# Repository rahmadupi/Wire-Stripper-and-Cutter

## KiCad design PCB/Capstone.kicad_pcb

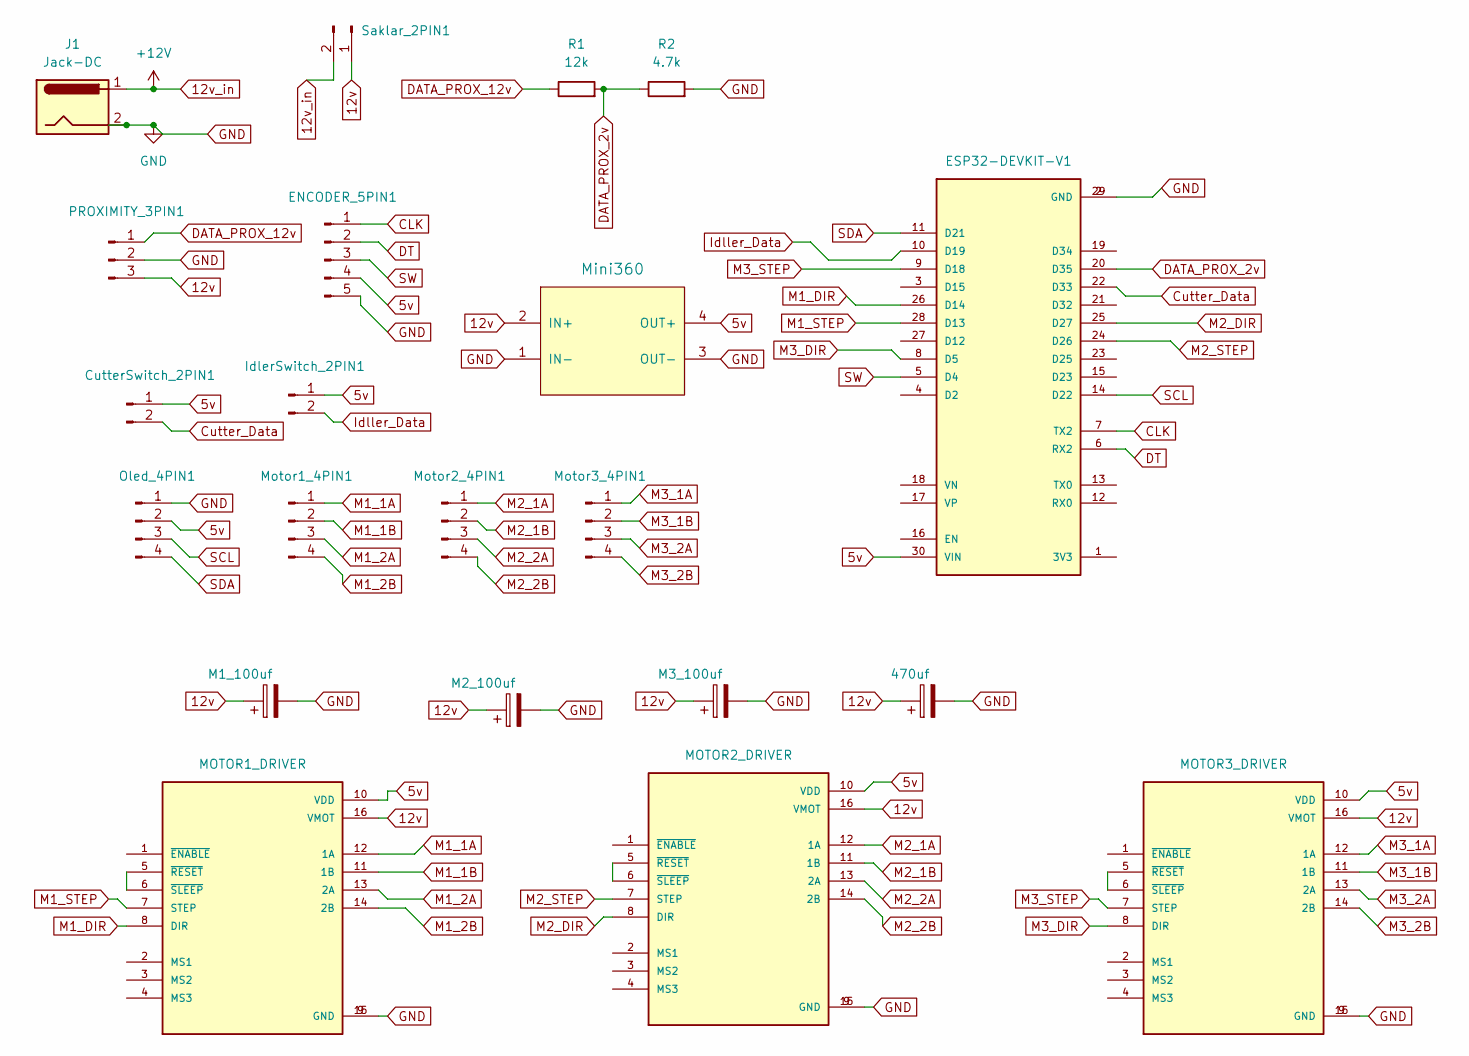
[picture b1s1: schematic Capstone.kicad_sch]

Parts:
C1: M1_100uf; CP_Radial_D4.0mm_P1.50mm
C2: M2_100uf; CP_Radial_D4.0mm_P1.50mm
C3: M3_100uf; CP_Radial_D4.0mm_P1.50mm
C4: 470uf; CP_Radial_D4.0mm_P1.50mm
CutterSwitch_2PIN1: Conn_01x02_Pin; JST_EH_B2B-EH-A_1x02_P2.50mm_Vertical
ENCODER_5PIN1: Conn_01x05_Pin; JST_EH_B5B-EH-A_1x05_P2.50mm_Vertical
IdlerSwitch_2PIN1: Conn_01x02_Pin; JST_EH_B2B-EH-A_1x02_P2.50mm_Vertical
J1: Jack-DC; BarrelJack_Horizontal
Motor1_4PIN1, Motor2_4PIN1, Motor3_4PIN1: Conn_01x04_Pin; JST_EH_B4B-EH-A_1x04_P2.50mm_Vertical
Oled_4PIN1: Conn_01x04_Pin; JST_EH_B4B-EH-A_1x04_P2.50mm_Vertical
PROXIMITY_3PIN1: Conn_01x03_Pin; JST_EH_B3B-EH-A_1x03_P2.50mm_Vertical
R1: 12k; R_Axial_DIN0204_L3.6mm_D1.6mm_P7.62mm_Horizontal
R2: 4.7k; R_Axial_DIN0204_L3.6mm_D1.6mm_P7.62mm_Horizontal
Saklar_2PIN1: Conn_01x02_Pin; JST_EH_B2B-EH-A_1x02_P2.50mm_Vertical
U1: ESP32-DEVKIT-V1; MODULE_ESP32_DEVKIT_V1; PARTREV N/A
U2: Mini360; Mini360_Module
U3: MOTOR1_DRIVER; MODULE_A4988_STEPPER_MOTOR_DRIVER_CARRIER_BLACK
U4: MOTOR2_DRIVER; MODULE_A4988_STEPPER_MOTOR_DRIVER_CARRIER_BLACK
U5: MOTOR3_DRIVER; MODULE_A4988_STEPPER_MOTOR_DRIVER_CARRIER_BLACK

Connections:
5v: CutterSwitch_2PIN1.1, ENCODER_5PIN1.4, IdlerSwitch_2PIN1.1, Oled_4PIN1.2, U1.30 (VIN), U2.4 (OUT+), U3.10 (VDD), U4.10 (VDD), U5.10 (VDD)
12v: C1.1, C2.1, C3.1, C4.1, PROXIMITY_3PIN1.3, Saklar_2PIN1.1, U2.2 (IN+), U3.16 (VMOT), U4.16 (VMOT), U5.16 (VMOT)
12v_in: J1.1, Saklar_2PIN1.2
CLK: ENCODER_5PIN1.1, U1.7 (TX2)
Cutter_Data: CutterSwitch_2PIN1.2, U1.22 (D33)
DATA_PROX_2v: R1.2, R2.1, U1.20 (D35)
DATA_PROX_12v: PROXIMITY_3PIN1.1, R1.1
DT: ENCODER_5PIN1.2, U1.6 (RX2)
GND: C1.2, C2.2, C3.2, C4.2, ENCODER_5PIN1.5, J1.2, Oled_4PIN1.1, PROXIMITY_3PIN1.2, R2.2, U1.2 (GND), U1.29 (GND), U2.1 (IN-), U2.3 (OUT-), U3.9 (GND), U3.15 (GND), U4.9 (GND), U4.15 (GND), U5.9 (GND), U5.15 (GND)
Idller_Data: IdlerSwitch_2PIN1.2, U1.10 (D19)
M1_1A: Motor1_4PIN1.1, U3.12 (1A)
M1_1B: Motor1_4PIN1.2, U3.11 (1B)
M1_2A: Motor1_4PIN1.3, U3.13 (2A)
M1_2B: Motor1_4PIN1.4, U3.14 (2B)
M1_DIR: U1.26 (D14), U3.8 (DIR)
M1_STEP: U1.28 (D13), U3.7 (STEP)
M2_1A: Motor2_4PIN1.1, U4.12 (1A)
M2_1B: Motor2_4PIN1.2, U4.11 (1B)
M2_2A: Motor2_4PIN1.3, U4.13 (2A)
M2_2B: Motor2_4PIN1.4, U4.14 (2B)
M2_DIR: U1.25 (D27), U4.8 (DIR)
M2_STEP: U1.24 (D26), U4.7 (STEP)
M3_1A: Motor3_4PIN1.1, U5.12 (1A)
M3_1B: Motor3_4PIN1.2, U5.11 (1B)
M3_2A: Motor3_4PIN1.3, U5.13 (2A)
M3_2B: Motor3_4PIN1.4, U5.14 (2B)
M3_DIR: U1.8 (D5), U5.8 (DIR)
M3_STEP: U1.9 (D18), U5.7 (STEP)
unnamed: U3.5 (~RESET), U3.6 (~SLEEP)
unnamed: U4.5 (~RESET), U4.6 (~SLEEP)
unnamed: U5.5 (~RESET), U5.6 (~SLEEP)
SCL: Oled_4PIN1.3, U1.14 (D22)
SDA: Oled_4PIN1.4, U1.11 (D21)
SW: ENCODER_5PIN1.3, U1.5 (D4)

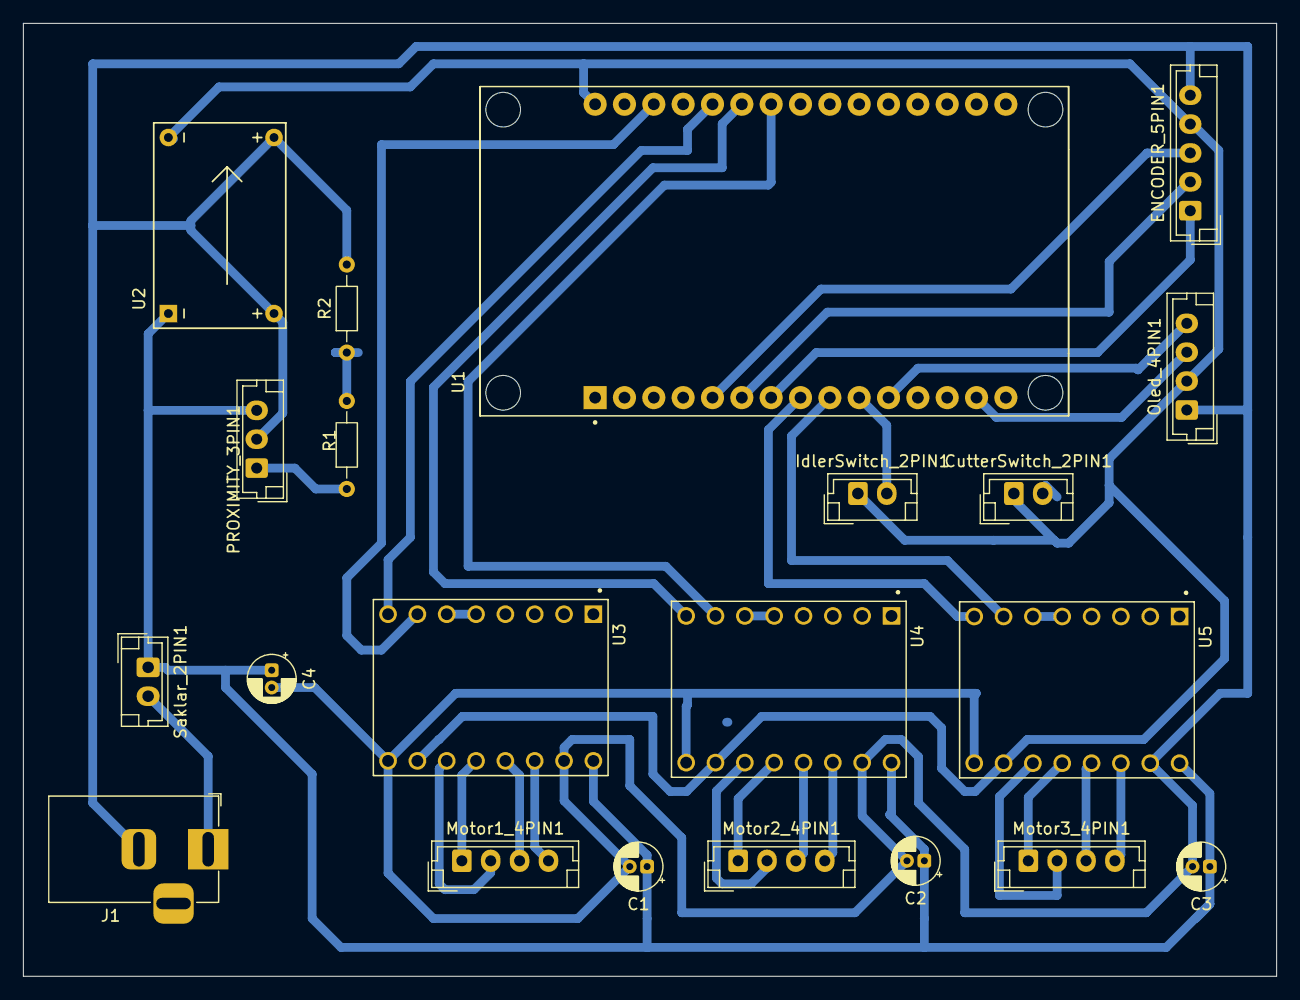
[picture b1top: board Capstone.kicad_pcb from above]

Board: 2 copper layers, 108.5 x 82.5 mm, 21 parts (0 on the bottom side), 34 nets.

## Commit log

2025-06-10 Display Done
2025-06-13 motor problem
2025-06-27 Selese
2025-06-27 add schematic
